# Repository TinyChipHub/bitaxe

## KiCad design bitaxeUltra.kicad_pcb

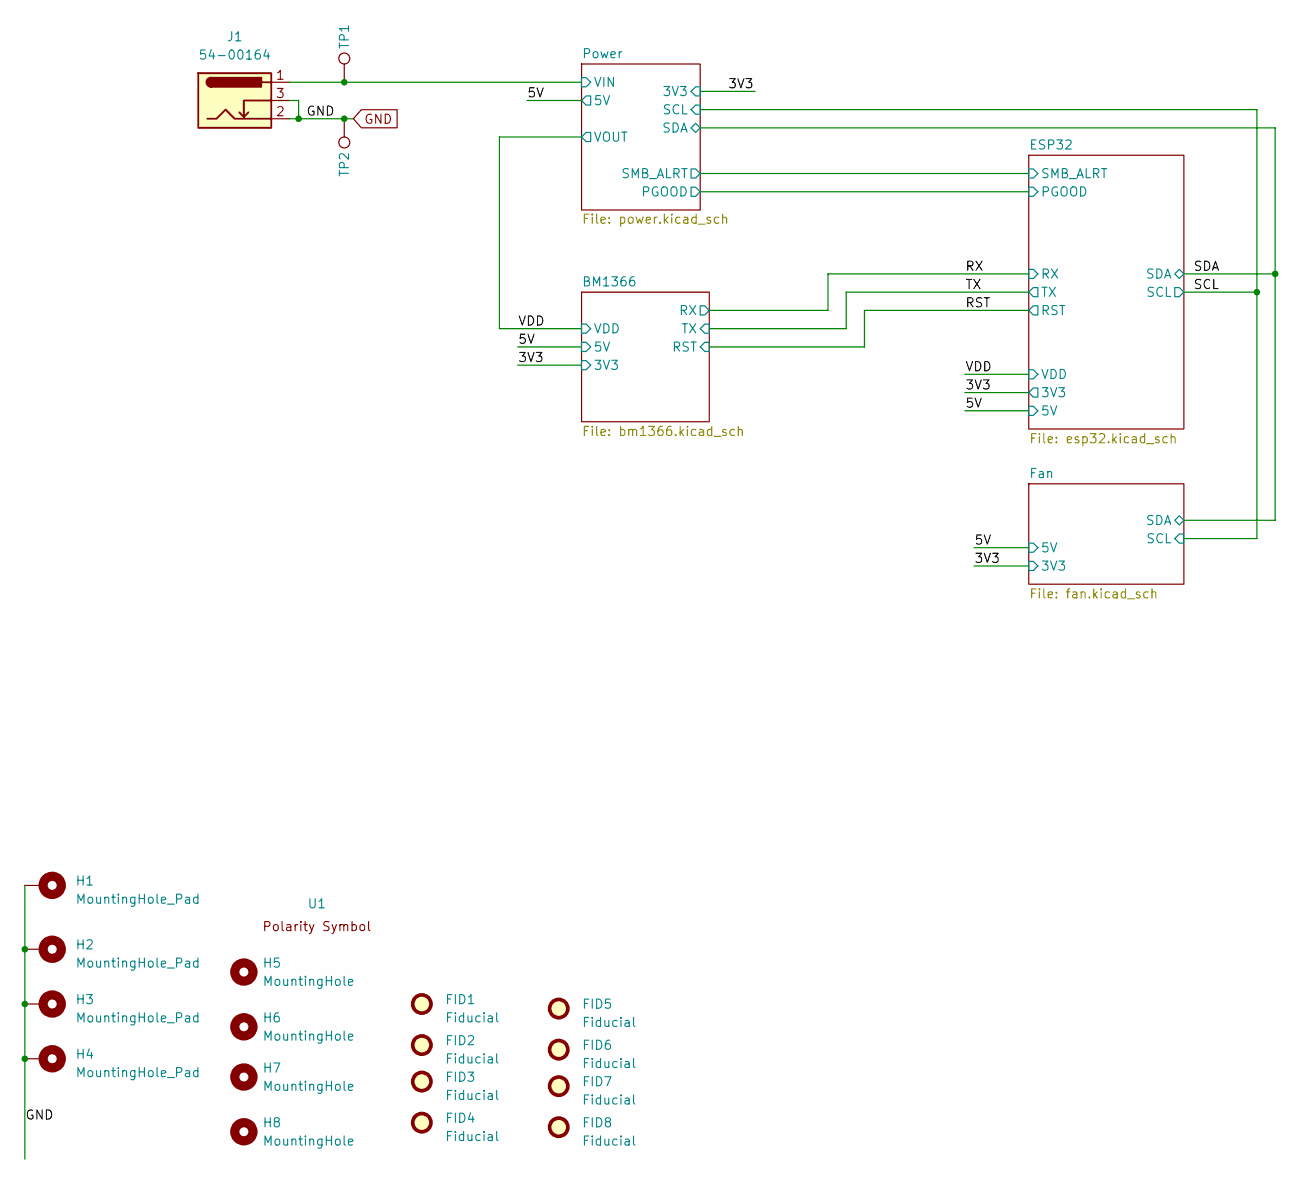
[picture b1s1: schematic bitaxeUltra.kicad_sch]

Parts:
FID1, FID2, FID3, FID4, FID5, FID6, FID7, FID8: Fiducial; Fiducial_1mm_Mask2mm
H1, H2, H3, H4: MountingHole_Pad; MountingHole_3mm_Pad_Via
H5, H6, H7, H8: MountingHole; MountingHole_3.5mm
J1: 54-00164; TENSILITY_54-00164; PARTNO 54-00164; LCSC C431534
TP1, TP2: TestPoint; TestPoint_Pad_D1.5mm
U1: polarity

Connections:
/5V: J1.1, TP1.1; also elsewhere on the board
GND: H1.1, H2.1, H3.1, H4.1, J1.2, J1.3, TP2.1; also elsewhere on the board

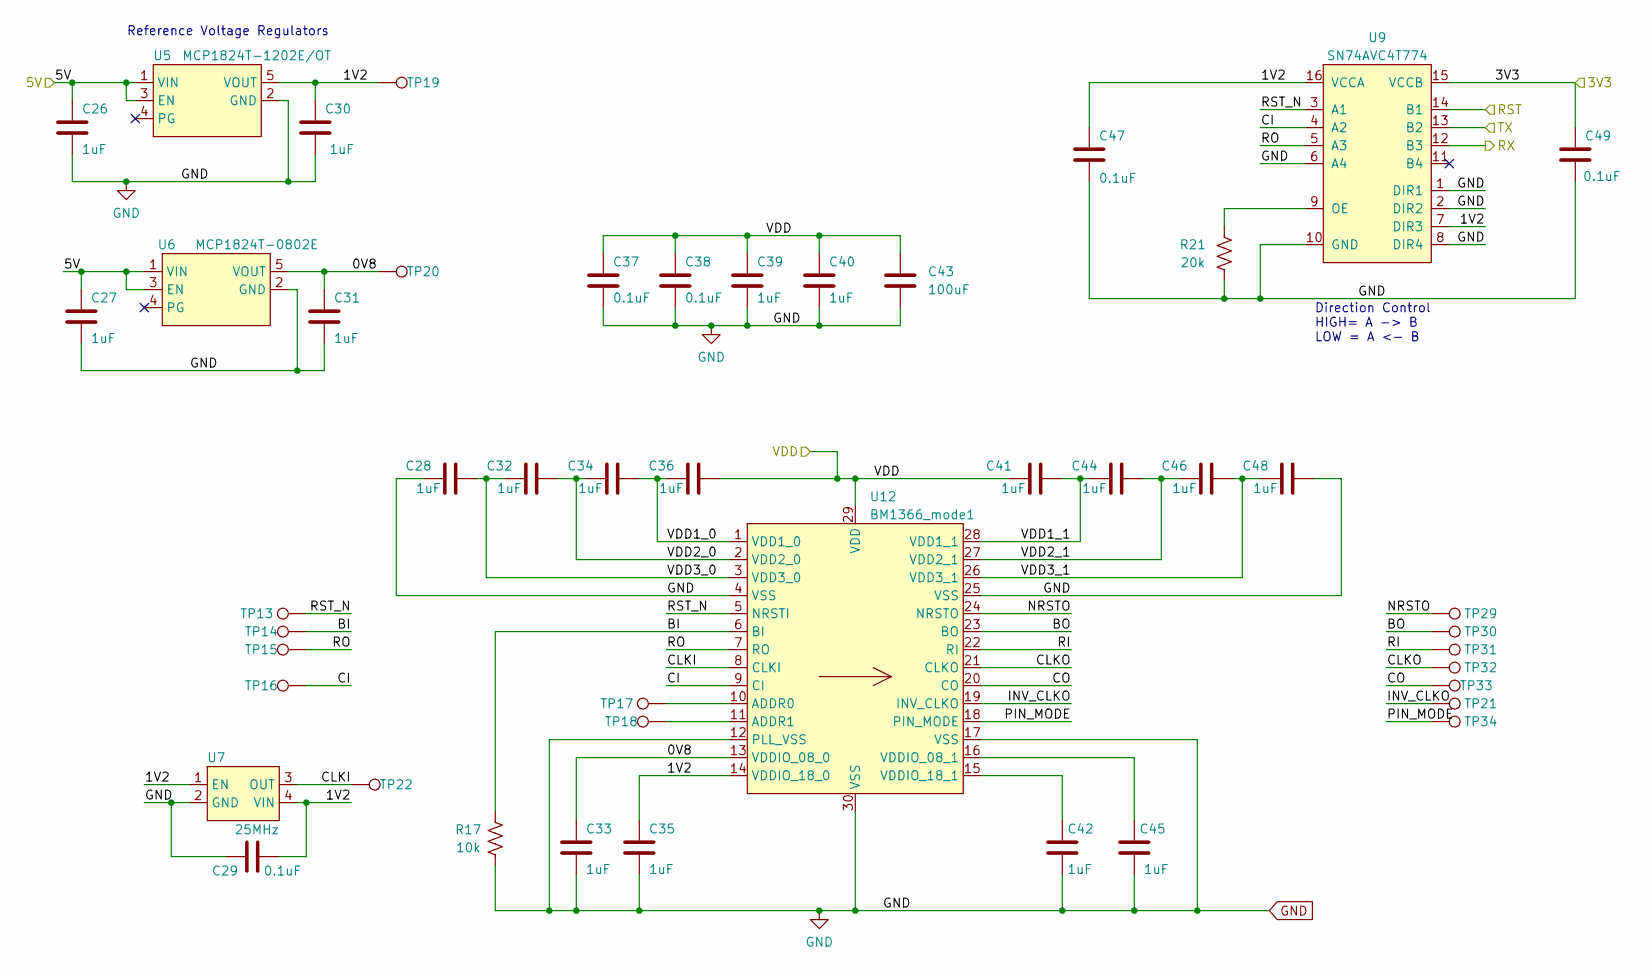
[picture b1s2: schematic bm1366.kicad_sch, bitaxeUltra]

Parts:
C26, C27, C28, C30, C31, C32, C33, C34, C35, C36, C39, C40, C41, C42, C44, C45, C46, C48: 1uF; C_0402_1005Metric; PARTNO EMK105BJ105MV-F
C29, C37, C38, C47, C49: 0.1uF; C_0402_1005Metric; PARTNO CL05A104KO5NNNC
C43: 100uF; C_1206_3216Metric; PARTNO CL31A107MQHNNNE
R17: 10k; R_0402_1005Metric; PARTNO RC0402JR-0710KL
R21: 20k; R_0402_1005Metric; PARTNO RC0402FR-0720KL
TP13, TP14, TP15, TP16, TP17, TP18, TP19, TP20, TP21, TP22, TP29, TP30, TP31, TP32, TP33, TP34: TestPoint; TestPoint_Pad_D1.5mm
U5: MCP1824T-1202E/OT; SOT-23-5; PARTNO MCP1824T-1202E/OT
U6: MCP1824T-0802E; SOT-23-5; PARTNO MCP1824T-0802E/OT
U7: 25MHz; O 25,0-JO32-B-1V3-1-T1-LF; PARTNO SX3M25.000E20F30THN; LCSC C5137262
U9: SN74AVC4T774; TSSOP-16_4.4x5mm_P0.65mm; PARTNO SN74AVC4T774PWR; LCSC C129363
U12: BM1366_mode1; BM1366

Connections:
/3V3: C49.1, U9.15 (VCCB); also elsewhere on the board
/5V: C26.1, C27.1, U5.1 (VIN), U5.3 (EN), U6.1 (VIN), U6.3 (EN); also elsewhere on the board
/BM1366/0V8: C31.1, C33.1, TP20.1, U6.5 (VOUT), U12.13 (VDDIO_08_0)
/BM1366/1V2: C29.2, C30.1, C35.1, C47.1, TP19.1, U5.5 (VOUT), U7.1 (EN), U7.4 (VIN), U9.7 (DIR3), U9.16 (VCCA), U12.14 (VDDIO_18_0)
/BM1366/BI: R17.2, TP14.1, U12.6 (BI)
/BM1366/BO: TP30.1, U12.23 (BO)
/BM1366/CI: TP16.1, U9.4 (A2), U12.9 (CI)
/BM1366/CLKI: TP22.1, U7.3 (OUT), U12.8 (CLKI)
/BM1366/CLKO: TP32.1, U12.21 (CLKO)
/BM1366/CO: TP33.1, U12.20 (CO)
/BM1366/INV_CLKO: TP21.1, U12.19 (INV_CLKO)
/BM1366/NRSTO: TP29.1, U12.24 (NRSTO)
/BM1366/PIN_MODE: TP34.1, U12.18 (PIN_MODE)
/BM1366/RI: TP31.1, U12.22 (RI)
/BM1366/RO: TP15.1, U9.5 (A3), U12.7 (RO)
/BM1366/RST_N: TP13.1, U9.3 (A1), U12.5 (NRSTI)
/BM1366/VDD1_0: C34.2, C36.1, U12.1 (VDD1_0)
/BM1366/VDD1_1: C41.2, C44.1, U12.28 (VDD1_1)
/BM1366/VDD2_0: C32.2, C34.1, U12.2 (VDD2_0)
/BM1366/VDD2_1: C44.2, C46.1, U12.27 (VDD2_1)
/BM1366/VDD3_0: C28.2, C32.1, U12.3 (VDD3_0)
/BM1366/VDD3_1: C46.2, C48.1, U12.26 (VDD3_1)
/RST: U9.14 (B1); also elsewhere on the board
/RX: U9.12 (B3); also elsewhere on the board
/TX: U9.13 (B2); also elsewhere on the board
/VDD: C36.2, C37.1, C38.1, C39.1, C40.1, C41.1, C43.1, U12.29 (VDD); also elsewhere on the board
GND: C26.2, C27.2, C28.1, C29.1, C30.2, C31.2, C33.2, C35.2, C37.2, C38.2, C39.2, C40.2, C42.2, C43.2, C45.2, C47.2, C48.2, C49.2, R17.1, R21.1, U5.2 (GND), U6.2 (GND), U7.2 (GND), U9.1 (DIR1), U9.2 (DIR2), U9.6 (A4), U9.8 (DIR4), U9.10 (GND), U12.4 (VSS), U12.12 (PLL_VSS), U12.17 (VSS), U12.25 (VSS), U12.30 (VSS); also elsewhere on the board
unnamed: R21.2, U9.9 (OE)
unnamed: TP17.1, U12.10 (ADDR0)
unnamed: TP18.1, U12.11 (ADDR1)
unnamed: C45.1, U12.16 (VDDIO_08_1)
unnamed: C42.1, U12.15 (VDDIO_18_1)

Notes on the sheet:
Reference Voltage Regulators
Direction Control HIGH= A -> B LOW = A <- B

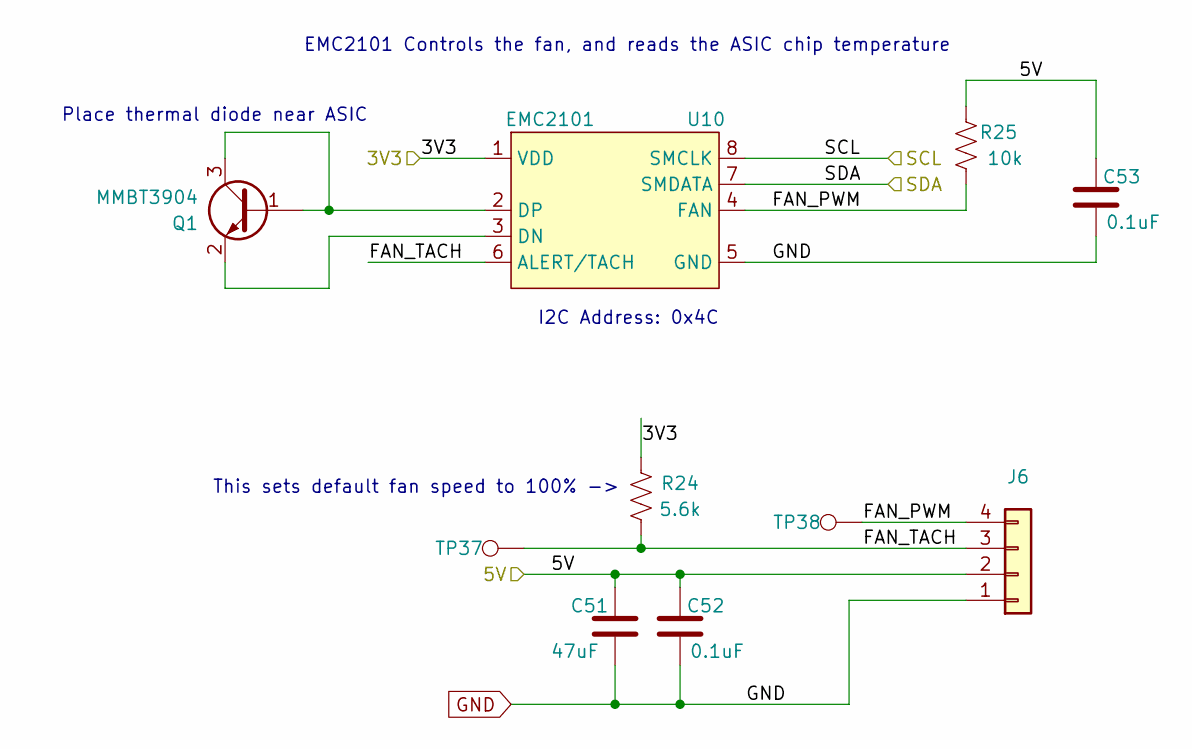
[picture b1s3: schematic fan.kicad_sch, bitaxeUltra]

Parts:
C51: 47uF; C_1210_3225Metric; PARTNO CL32A476KOJNNNE
C52, C53: 0.1uF; C_0402_1005Metric; PARTNO CL05A104KO5NNNC
J6: Conn_01x04; 470531000; PARTNO 0470531000
Q1: MMBT3904; TRANS_MMBT3904LP-7B; PARTNO MMBT3904LP-7B; LCSC C460099
R24: 5.6k; R_0402_1005Metric; PARTNO RC0402FR-135K6L
R25: 10k; R_0402_1005Metric; PARTNO RC0402JR-0710KL
TP37, TP38: TestPoint; TestPoint_Pad_D1.5mm
U10: EMC2101; TSSOP-8_3x3mm_P0.65mm; PARTNO EMC2101-R-ACZL-TR

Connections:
/3V3: R24.2, U10.1 (VDD); also elsewhere on the board
/5V: C51.1, C52.1, C53.1, J6.2, R25.2; also elsewhere on the board
/Fan/FAN_PWM: J6.4, R25.1, TP38.1, U10.4 (FAN)
/Fan/FAN_TACH: J6.3, R24.1, TP37.1, U10.6 (ALERT/TACH)
/SCL: U10.8 (SMCLK); also elsewhere on the board
/SDA: U10.7 (SMDATA); also elsewhere on the board
GND: C51.2, C52.2, C53.2, J6.1, U10.5 (GND); also elsewhere on the board
unnamed: Q1.1 (B), Q1.3 (C), U10.2 (DP)
unnamed: Q1.2 (E), U10.3 (DN)

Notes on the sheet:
Place thermal diode near ASIC
EMC2101 Controls the fan, and reads the ASIC chip temperature
This sets default fan speed to 100% ->
I2C Address: 0x4C

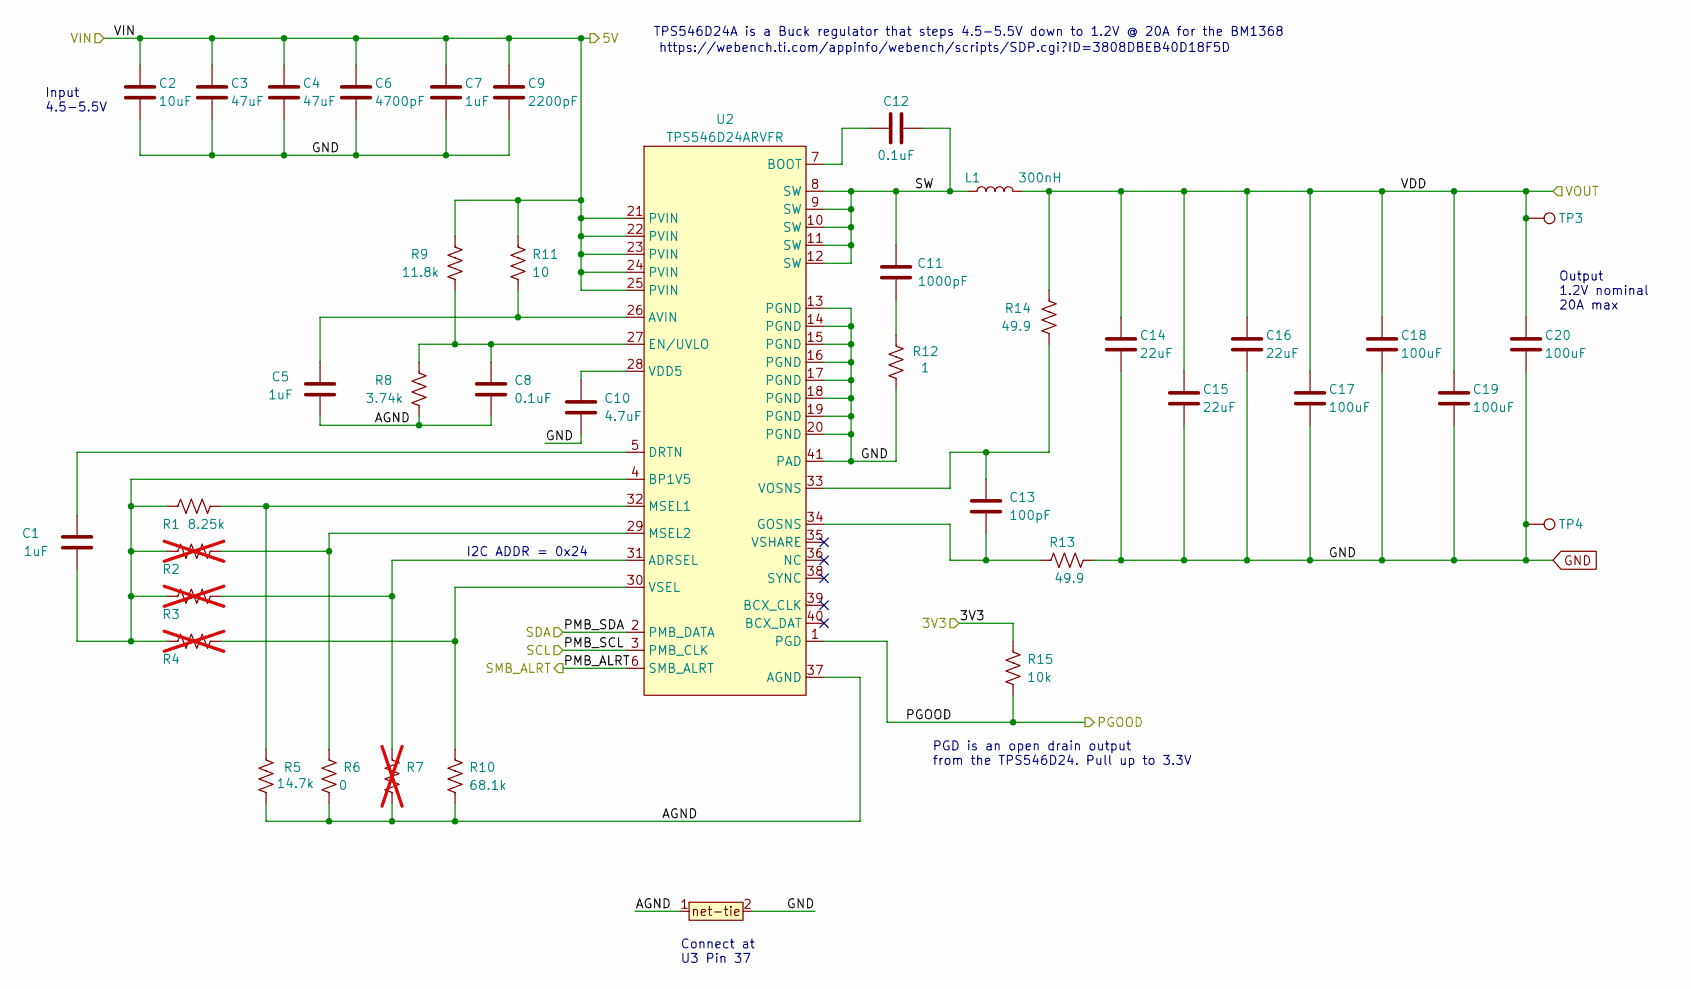
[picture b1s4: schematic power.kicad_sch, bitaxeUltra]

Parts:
C1, C5, C7: 1uF; C_0402_1005Metric; PARTNO EMK105BJ105MV-F
C2: 10uF; C_0805_2012Metric; PARTNO CL21A106KOQNNNE
C3, C4: 47uF; C_1210_3225Metric; PARTNO CL32A476KOJNNNE
C6: 4700pF; C_0402_1005Metric; PARTNO CC0402KRX7R8BB472
C8, C12: 0.1uF; C_0402_1005Metric; PARTNO CL05A104KO5NNNC
C9: 2200pF; C_0402_1005Metric; PARTNO GRM155R61H222KA01D
C10: 4.7uF; C_0402_1005Metric; PARTNO CL05A475MP5NRNC
C11: 1000pF; C_0805_2012Metric; PARTNO CC0805KRX7R9BB102
C13: 100pF; C_0402_1005Metric; PARTNO CC0402JRNPO9BN101
C14, C15, C16: 22uF; C_0805_2012Metric; PARTNO GRM21BR61A226ME44L
C17, C18, C19, C20: 100uF; C_1206_3216Metric; PARTNO CL31A107MQHNNNE
L1: 300nH; SLC1175-271MEC_COC; PARTNO YLSI100808-R22K; Mouser 994-SLC1175-271MEC
R1: 8.25k; R_0402_1005Metric; PARTNO RC0402FR-078K25L
R2, R3, R4, R7: R_0402_1005Metric; not fitted
R5: 14.7k; R_0402_1005Metric; PARTNO RC0402FR-0714K7L
R6: 0; R_0402_1005Metric; PARTNO RC0402JR-070RL
R8: 3.74k; R_0402_1005Metric; PARTNO RC0402FR-073K74L
R9: 11.8k; R_0402_1005Metric; PARTNO RC0402FR-0711K8L
R10: 68.1k; R_0402_1005Metric; PARTNO RC0402FR-0768K1L
R11: 10; R_0402_1005Metric; PARTNO RC0402FR-0710RL
R12: 1; R_1206_3216Metric; PARTNO CSR1206FT1R00
R13, R14: 49.9; R_0402_1005Metric; PARTNO RC0402FR-0749R9L
R15: 10k; R_0402_1005Metric; PARTNO RC0402JR-0710KL
T1: net-tie; NetTie-0.25mm
TP3, TP4: TestPoint; TestPoint_Pad_D1.5mm
U2: TPS546D24ARVFR; LQFN40-CLIP; PARTNO TPS546D24ARVFR

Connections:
/3V3: R15.2; also elsewhere on the board
/5V: C2.1, C3.1, C4.1, C6.1, C7.1, C9.1, R9.1, R11.1, U2.21 (PVIN), U2.22 (PVIN), U2.23 (PVIN), U2.24 (PVIN), U2.25 (PVIN); also elsewhere on the board
/Power/AGND: C5.1, C8.2, R5.1, R6.2, R7.2, R8.2, R10.2, T1.1, U2.37 (AGND)
/Power/PGOOD: R15.1, U2.1 (PGD); also elsewhere on the board
/Power/PMB_ALRT: U2.6 (SMB_ALRT); also elsewhere on the board
/Power/SW: C11.2, C12.2, L1.1, U2.8 (SW), U2.9 (SW), U2.10 (SW), U2.11 (SW), U2.12 (SW)
/SCL: U2.3 (PMB_CLK); also elsewhere on the board
/SDA: U2.2 (PMB_DATA); also elsewhere on the board
/VDD: C14.1, C15.1, C16.1, C17.1, C18.1, C19.1, C20.1, L1.2, R14.1, TP3.1; also elsewhere on the board
GND: C2.2, C3.2, C4.2, C6.2, C7.2, C9.2, C10.2, C14.2, C15.2, C16.2, C17.2, C18.2, C19.2, C20.2, R12.1, R13.2, T1.2, TP4.1, U2.13 (PGND), U2.14 (PGND), U2.15 (PGND), U2.16 (PGND), U2.17 (PGND), U2.18 (PGND), U2.19 (PGND), U2.20 (PGND), U2.41 (PAD); also elsewhere on the board
unnamed: C11.1, R12.2
unnamed: R3.2, R7.1, U2.31 (ADRSEL)
unnamed: C5.2, R11.2, U2.26 (AVIN)
unnamed: C12.1, U2.7 (BOOT)
unnamed: C1.2, R1.1, R2.1, R3.1, R4.1, U2.4 (BP1V5)
unnamed: C1.1, U2.5 (DRTN)
unnamed: C8.1, R8.1, R9.2, U2.27 (EN/UVLO)
unnamed: C13.2, R13.1, U2.34 (GOSNS)
unnamed: R1.2, R5.2, U2.32 (MSEL1)
unnamed: R2.2, R6.1, U2.29 (MSEL2)
unnamed: C10.1, U2.28 (VDD5)
unnamed: C13.1, R14.2, U2.33 (VOSNS)
unnamed: R4.2, R10.1, U2.30 (VSEL)

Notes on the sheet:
TPS546D24A is a Buck regulator that steps 4.5-5.5V down to 1.2V @ 20A for the BM1368
https://webench.ti.com/appinfo/webench/scripts/SDP.cgi?ID=3808DBEB40D18F5D
Input 4.5-5.5V
PGD is an open drain output from the TPS546D24. Pull up to 3.3V
I2C ADDR = 0x24
Output 1.2V nominal 20A max
Connect at U3 Pin 37

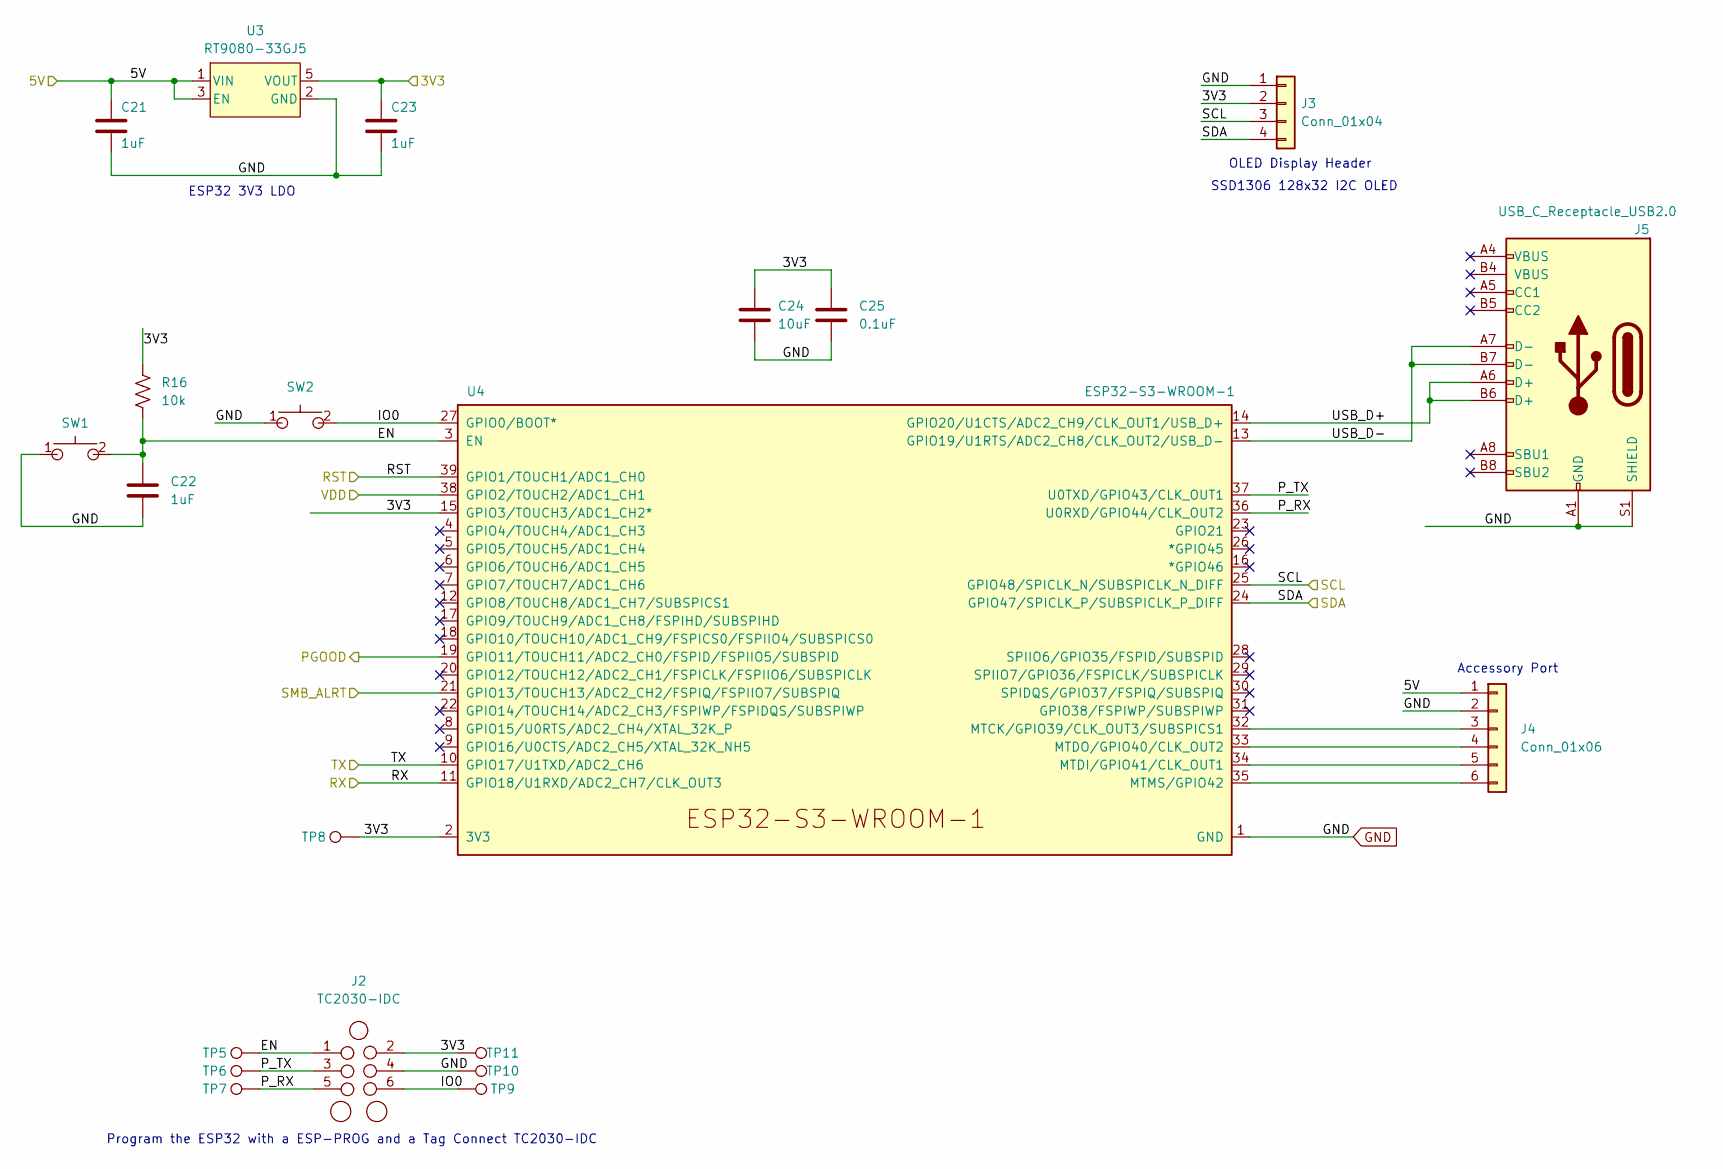
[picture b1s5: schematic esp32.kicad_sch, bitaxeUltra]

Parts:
C21, C22, C23: 1uF; C_0402_1005Metric; PARTNO EMK105BJ105MV-F
C24: 10uF; C_0805_2012Metric; PARTNO CL21A106KOQNNNE
C25: 0.1uF; C_0402_1005Metric; PARTNO CL05A104KO5NNNC
J2: TC2030-IDC; Tag-Connect_TC2030-IDC-NL_2x03_P1.27mm_Vertical
J3: Conn_01x04; PinHeader_1x04_P2.54mm_Vertical_shifted; PARTNO NPTC041KFXC-RC
J4: Conn_01x06; PinHeader_1x06_P2.54mm_Vertical
J5: USB_C_Receptacle_USB2.0; USB_C_Receptacle_GCT_USB4105-xx-A; PARTNO USB4105-GF-A
R16: 10k; R_0402_1005Metric; PARTNO RC0402JR-0710KL
SW1, SW2: GT-TC029B-H025-L1N; SW_CS1213AGF260_CRS; PARTNO CS1213AGF260
TP5, TP6, TP7, TP8, TP9, TP10, TP11: TestPoint; TestPoint_Pad_D1.5mm
U3: RT9080-33GJ5; PARTNO RT9080-33GJ5
U4: ESP32-S3-WROOM-1; PARTNO ESP32-S3-WROOM-1-N16R8

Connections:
/3V3: C23.1, C24.1, C25.1, J2.2, J3.2, R16.1, TP8.1, TP11.1, U3.5 (VOUT), U4.2 (3V3), U4.15 (GPIO3/TOUCH3/ADC1_CH2*); also elsewhere on the board
/5V: C21.1, J4.1, U3.1 (VIN), U3.3 (EN); also elsewhere on the board
/ESP32/EN: C22.1, J2.1, R16.2, SW1.2, TP5.1, U4.3 (EN)
/ESP32/IO0: J2.6, SW2.2, TP9.1, U4.27 (GPIO0/BOOT*)
/ESP32/P_RX: J2.5, TP7.1, U4.36 (U0RXD/GPIO44/CLK_OUT2)
/ESP32/P_TX: J2.3, TP6.1, U4.37 (U0TXD/GPIO43/CLK_OUT1)
/ESP32/USB_D+: J5.A6 (D+), J5.B6 (D+), U4.14 (GPIO20/U1CTS/ADC2_CH9/CLK_OUT1/USB_D+)
/ESP32/USB_D-: J5.A7 (D-), J5.B7 (D-), U4.13 (GPIO19/U1RTS/ADC2_CH8/CLK_OUT2/USB_D-)
/Power/PGOOD: U4.19 (GPIO11/TOUCH11/ADC2_CH0/FSPID/FSPIIO5/S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); also elsewhere on the board
/Power/PMB_ALRT: U4.21 (GPIO13/TOUCH13/ADC2_CH2/FSPIQ/FSPIIO7/S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); also elsewhere on the board
/RST: U4.39 (GPIO1/TOUCH1/ADC1_CH0); also elsewhere on the board
/RX: U4.11 (GPIO18/U1RXD/ADC2_CH7/CLK_OUT3); also elsewhere on the board
/SCL: J3.3, U4.25 (GPIO48/SPICLK_N/SUBSPICLK_N_DIFF); also elsewhere on the board
/SDA: J3.4, U4.24 (GPIO47/SPICLK_P/SUBSPICLK_P_DIFF); also elsewhere on the board
/TX: U4.10 (GPIO17/U1TXD/ADC2_CH6); also elsewhere on the board
/VDD: U4.38 (GPIO2/TOUCH2/ADC1_CH1); also elsewhere on the board
GND: C21.2, C22.2, C23.2, C24.2, C25.2, J2.4, J3.1, J4.2, J5.A1 (GND), J5.B1 (GND), J5.S1 (SHIELD), SW1.1, SW2.1, TP10.1, U3.2 (GND), U4.1 (GND), U4.40 (GND), U4.41 (GND); also elsewhere on the board
unnamed: J4.3, U4.32 (MTCK/GPIO39/CLK_OUT3/SUBSPICS1)
unnamed: J4.4, U4.33 (MTDO/GPIO40/CLK_OUT2)
unnamed: J4.5, U4.34 (MTDI/GPIO41/CLK_OUT1)
unnamed: J4.6, U4.35 (MTMS/GPIO42)

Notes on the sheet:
Accessory Port
ESP32 3V3 LDO
Program the ESP32 with a ESP-PROG and a Tag Connect TC2030-IDC
SSD1306 128x32 I2C OLED
OLED Display Header

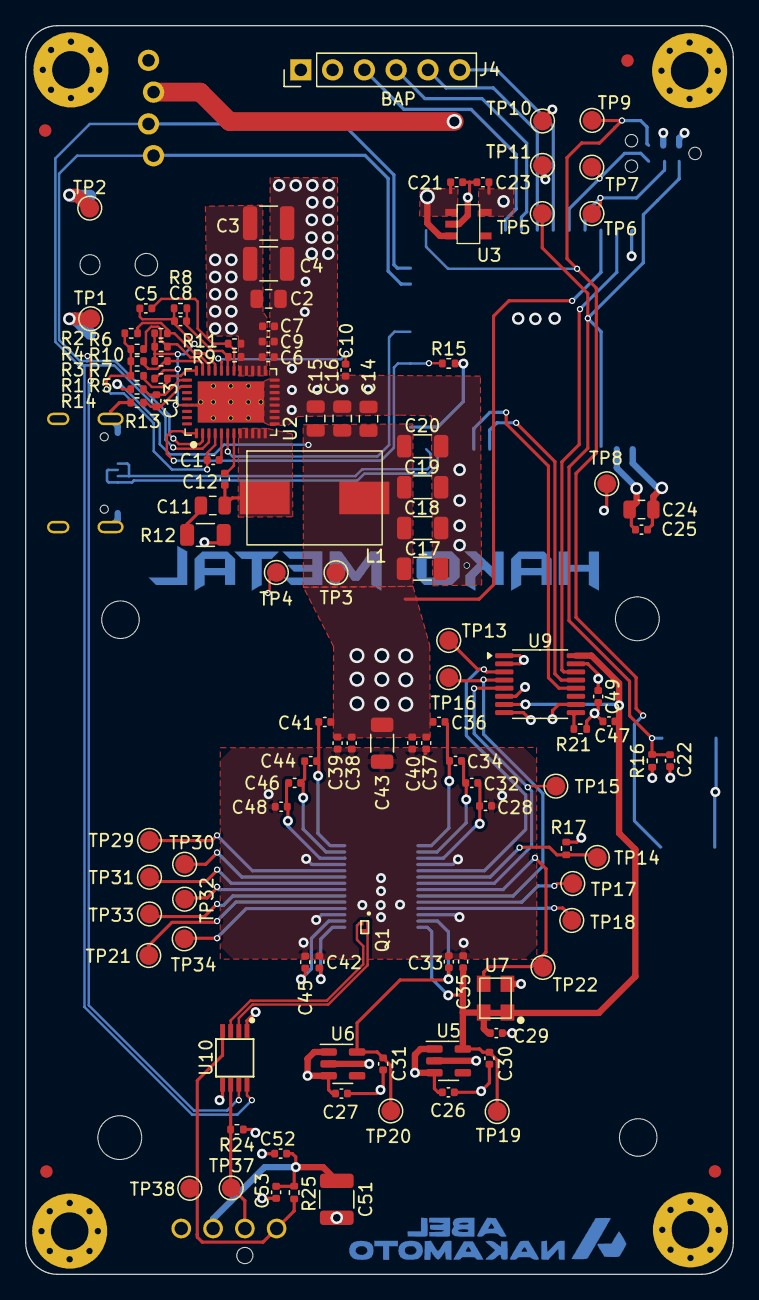
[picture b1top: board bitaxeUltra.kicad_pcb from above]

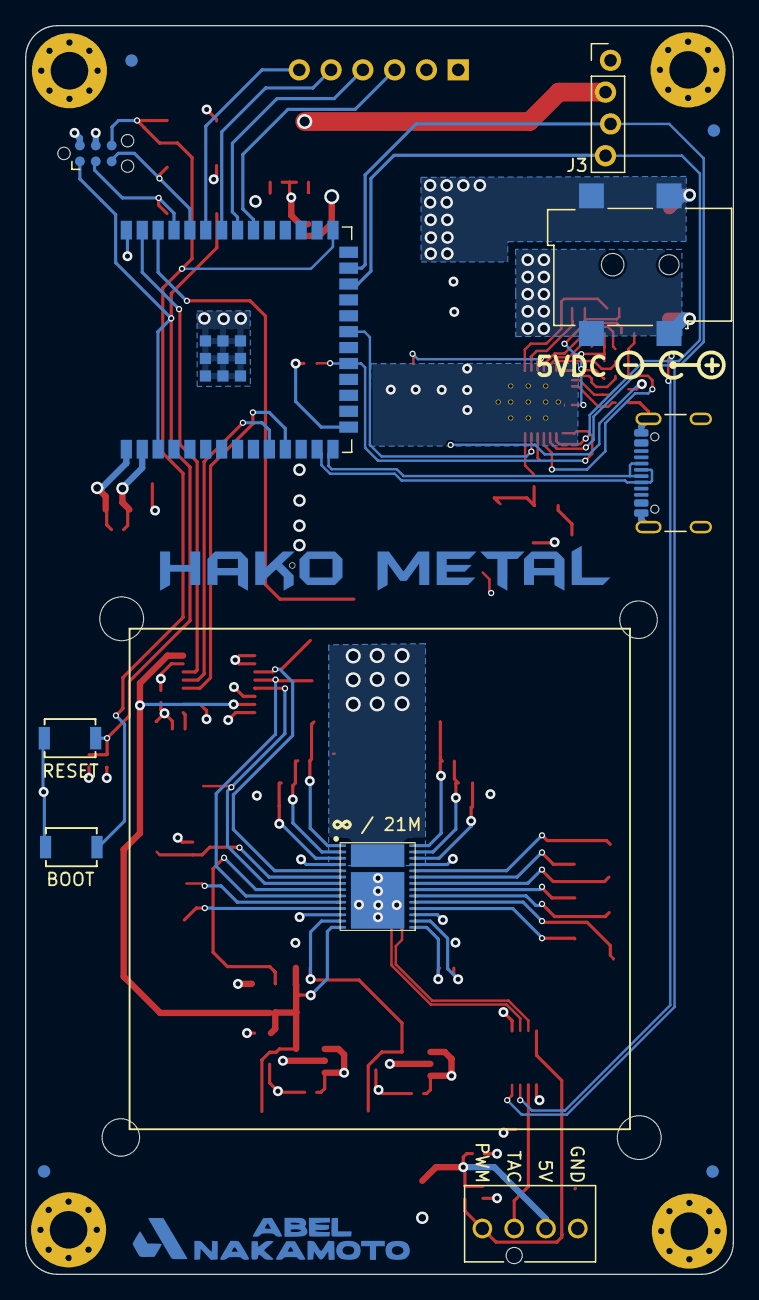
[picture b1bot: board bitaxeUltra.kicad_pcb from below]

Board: 4 copper layers, 56.5 x 99.8 mm, 138 parts (14 on the bottom side), 65 nets.

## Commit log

2024-06-21 *Move barrel jack to fix the enclosure; *Add logo
2024-07-15 Add TCH logo
2025-04-07 add fixture
2025-04-18 change the paste layer for the chip
2025-08-22 Add BitcoinMerch Logo
2026-01-25 Change logo for to B
2026-01-28 finalize
